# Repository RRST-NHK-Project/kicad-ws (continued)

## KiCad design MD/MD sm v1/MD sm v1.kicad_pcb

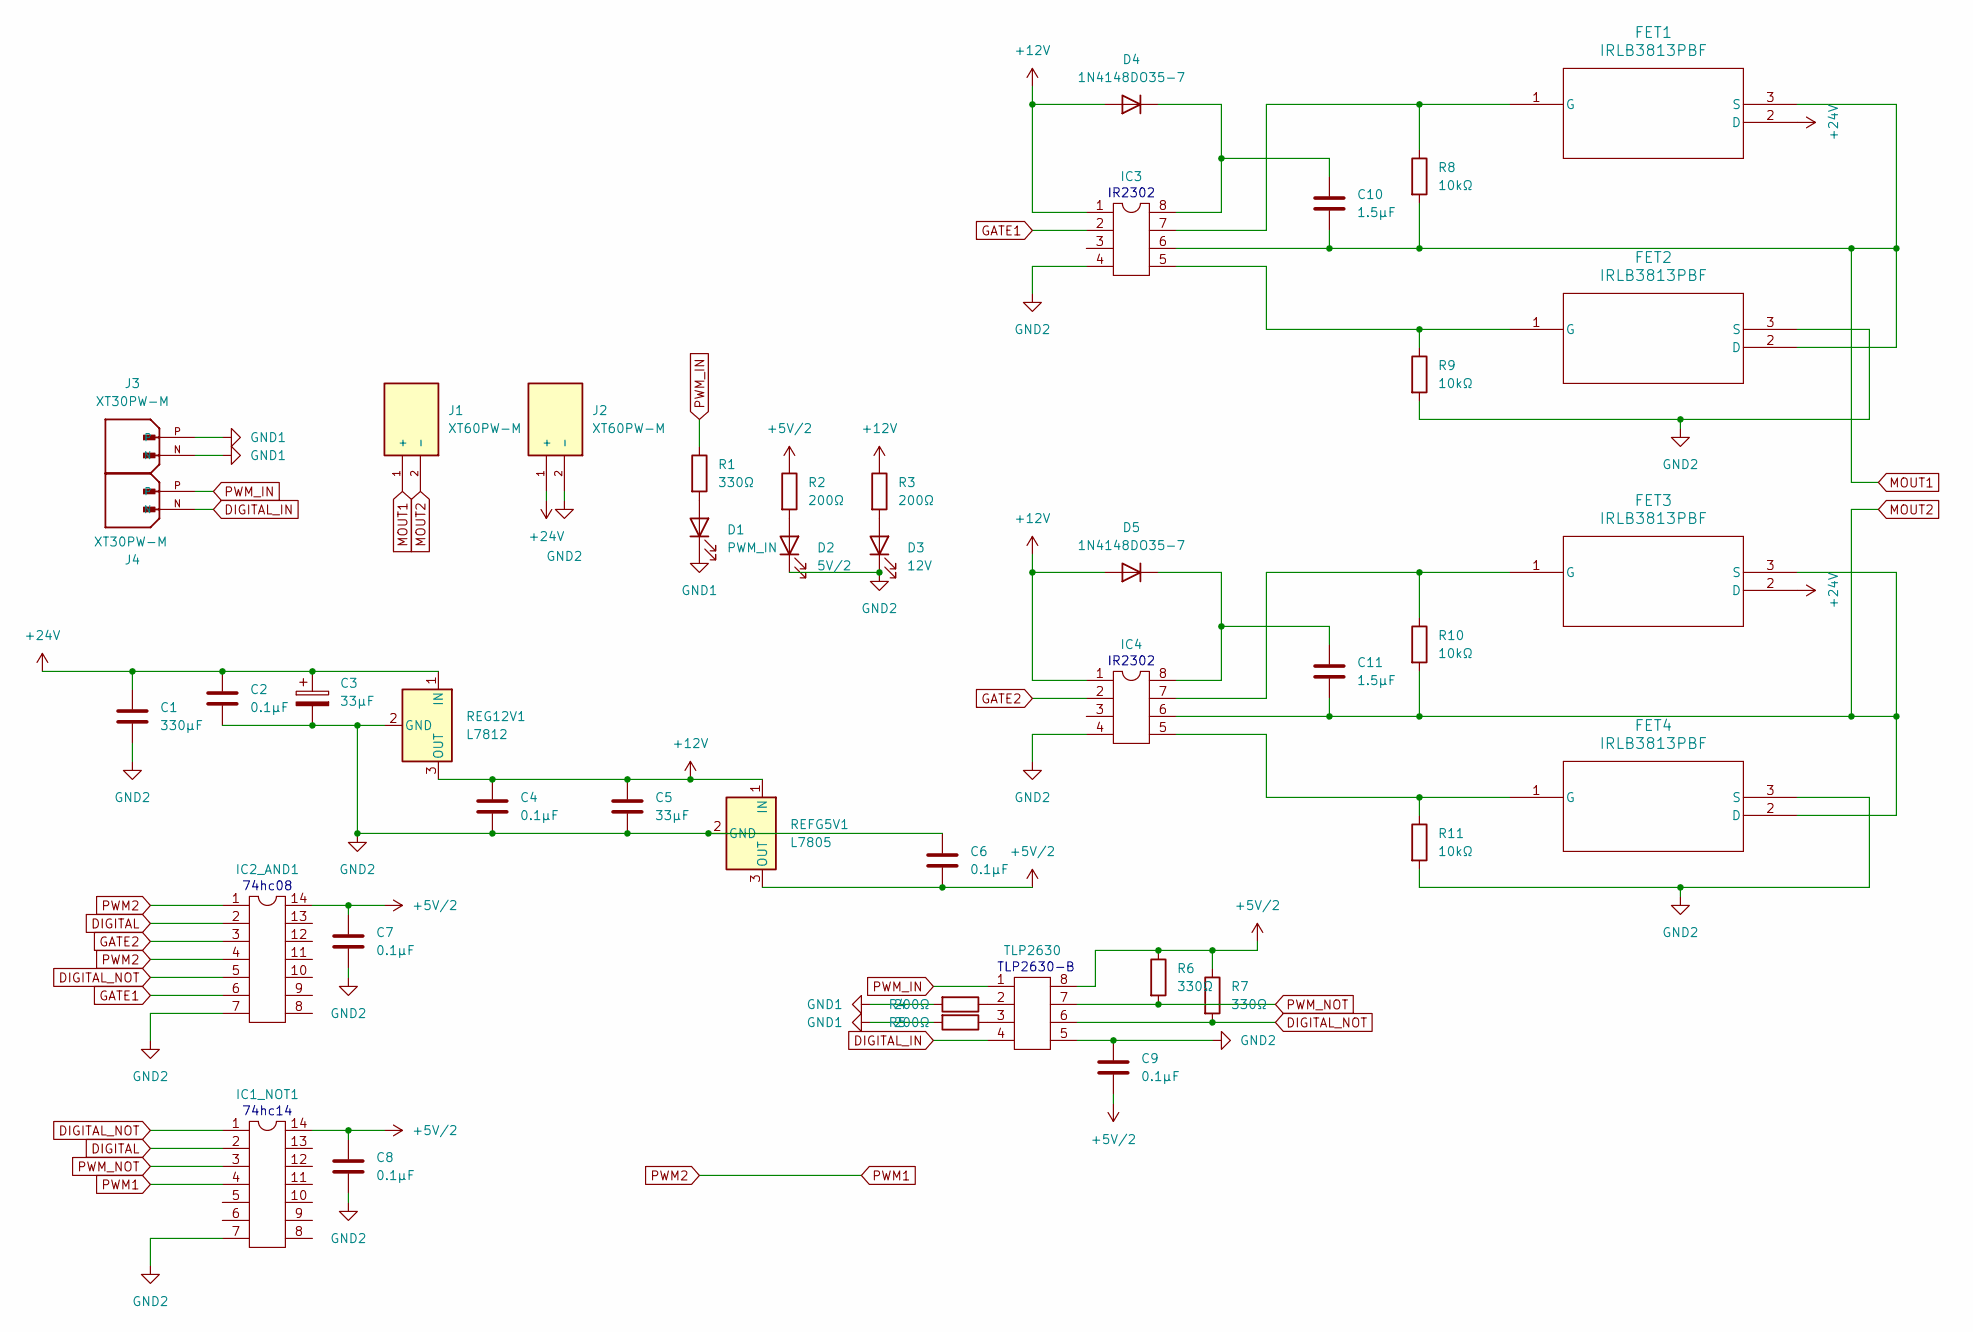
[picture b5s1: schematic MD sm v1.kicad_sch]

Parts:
C1: 330μF; CP_Radial_D8.0mm_P3.50mm
C2, C4, C6, C8, C9: 0.1μF; C_0603_1608Metric
C3, C5: 33μF; CP_Radial_D5.0mm_P2.00mm
C7: 0.1μF; C_0504_1310Metric_Pad0.83x1.28mm_HandSolder
C10, C11: 1.5μF; C_0805_2012Metric
D1: PWM_IN; LED_0805_2012Metric
D2: 5V/2; LED_0805_2012Metric
D3: 12V; LED_0805_2012Metric
D4, D5: 1N4148DO35-7; D_SOD-123
FET1, FET2, FET3, FET4: IRLB3813PBF; PG-TO220-3_INF
IC1_NOT1, IC2_AND1: DIP-14_W7.62mm
IC3, IC4: SOIC-8_3.9x4.9mm_P1.27mm
J1, J2: XT60PW-M; AMASS_XT60PW-M; PARTREV V1.2
J3, J4: XT30PW-M; AMASS_XT30PW-M; PARTREV 1.2
R1, R6, R7: 330Ω; R_0603_1608Metric
R2, R3, R4, R5: 200Ω; R_0603_1608Metric
R8, R9, R10, R11: 10kΩ; R_0603_1608Metric
REFG5V1: L7805; SOIC-14_3.9x8.7mm_P1.27mm
REG12V1: L7812; SOIC-14_3.9x8.7mm_P1.27mm
TLP2630: DIP-8_W7.62mm

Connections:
+5V/2: C6.2, C7.1, C8.1, C9.2, IC1_NOT1.14, IC2_AND1.14, R2.1, R6.1, R7.1, REFG5V1.3 (OUT), TLP2630.8
+12V: C4.1, C5.1, D4.2 (A), D5.2 (A), IC3.1, IC4.1, R3.1, REFG5V1.1 (IN), REG12V1.3 (OUT)
+24V: C1.1, C2.1, C3.1, FET1.2 (D), FET3.2 (D), J2.1 (+), REG12V1.1 (IN)
DIGITAL: IC1_NOT1.2, IC2_AND1.2
DIGITAL_IN: J4.N, TLP2630.4
DIGITAL_NOT: IC1_NOT1.1, IC2_AND1.5, R7.2, TLP2630.6
GATE1: IC2_AND1.6, IC3.2
GATE2: IC2_AND1.3, IC4.2
GND1: D1.1 (K), J3.N, J3.P, R4.2, R5.2
GND2: C1.2, C2.2, C3.2, C4.2, C5.2, C6.1, C7.2, C8.2, C9.1, D2.1 (K), D3.1 (K), FET2.3 (S), FET4.3 (S), IC1_NOT1.7, IC2_AND1.7, IC3.4, IC4.4, J2.2 (-), R9.2, R11.2, REFG5V1.2 (GND), REG12V1.2 (GND), TLP2630.5
MOUT1: C10.2, FET1.3 (S), FET2.2 (D), IC3.6, J1.1 (+), R8.2
MOUT2: C11.2, FET3.3 (S), FET4.2 (D), IC4.6, J1.2 (-), R10.2
unnamed: D1.2 (A), R1.2
unnamed: D2.2 (A), R2.2
unnamed: D3.2 (A), R3.2
unnamed: C10.1, D4.1 (K), IC3.8
unnamed: C11.1, D5.1 (K), IC4.8
unnamed: FET1.1 (G), IC3.7, R8.1
unnamed: FET2.1 (G), IC3.5, R9.1
unnamed: FET3.1 (G), IC4.7, R10.1
unnamed: FET4.1 (G), IC4.5, R11.1
unnamed: R4.1, TLP2630.2
unnamed: R5.1, TLP2630.3
PWM1: IC1_NOT1.4, IC2_AND1.1, IC2_AND1.4
PWM_IN: J4.P, R1.1, TLP2630.1
PWM_NOT: IC1_NOT1.3, R6.2, TLP2630.7

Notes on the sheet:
74hc08
IR2302
74hc14
TLP2630-B

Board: 2 copper layers, 42 parts (0 on the bottom side), 26 nets, no tracks yet.
